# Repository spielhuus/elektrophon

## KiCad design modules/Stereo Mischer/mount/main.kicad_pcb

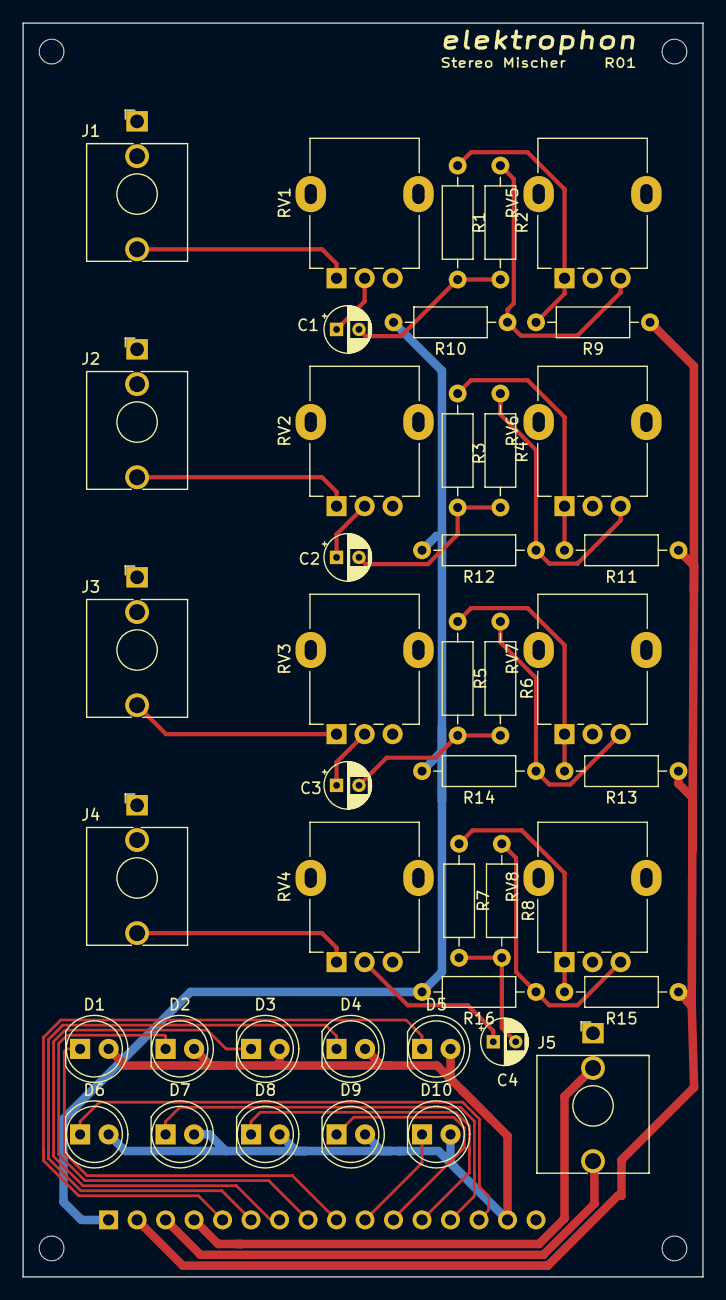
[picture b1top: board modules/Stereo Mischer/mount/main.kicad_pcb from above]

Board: 2 copper layers, 60.6 x 111.8 mm, 44 parts (1 on the bottom side), 36 nets.

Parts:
C1, C2, C3, C4: 4u7; CP_Radial_D4.0mm_P2.00mm
D1, D2, D3, D4, D5, D6, D7, D8, D9, D10: LED; LED_D5.0mm
J1: #1; Jack_3.5mm_WQP-PJ398SM_Vertical
J2: #2; Jack_3.5mm_WQP-PJ398SM_Vertical
J3: #3; Jack_3.5mm_WQP-PJ398SM_Vertical
J4: #4; Jack_3.5mm_WQP-PJ398SM_Vertical
J5: STEREO_OUT; Jack_3.5mm_WQP-PJ301BM_Vertical
J6: Conn_01x16_Male; PinHeader_1x16_P2.54mm_Vertical
R1, R2, R3, R4, R5, R6, R7, R8, R9, R10, R11, R12, R13, R14, R15, R16: 10k; R_Axial_DIN0207_L6.3mm_D2.5mm_P10.16mm_Horizontal
RV1, RV2, RV3, RV4: 10k; Potentiometer_Alpha_RD901F-40-00D_Single_Vertical
RV5, RV6, RV7, RV8: 25k; Potentiometer_Alpha_RD901F-40-00D_Single_Vertical

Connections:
+15V: D1.2, D2.2, D3.2, D4.2, D5.2, D6.2, D7.2, D8.2, D9.2, D10.2, J6.15
/LED_L_1: D6.1, J6.14
/LED_L_2: D7.1, J6.13
/LED_L_3: D8.1, J6.12
/LED_L_4: D9.1, J6.11
/LED_L_5: D10.1, J6.10
/LED_R_1: D1.1, J6.9
/LED_R_2: D2.1, J6.8
/LED_R_3: D3.1, J6.7
/LED_R_4: D4.1, J6.6
/LED_R_5: D5.1, J6.5
/LEFT: J6.2, R9.1, R11.1, R13.1, R15.1
/RIGHT: J6.1, R10.2, R12.2, R14.2, R16.2
/STEREO_L: J5.R, J6.4
/STEREO_R: J5.T, J6.3
GND: J1.S, J2.S, J3.S, J4.S, J5.S, J6.16, RV1.3, RV2.3, RV3.3, RV4.3, RV5.2, RV6.2, RV7.2, RV8.2
unnamed: C1.1, RV1.2
unnamed: C1.2, R1.2, R2.2
unnamed: C2.1, RV2.2
unnamed: C2.2, R3.2, R4.2
unnamed: C3.1, RV3.2
unnamed: C3.2, R5.2, R6.2
unnamed: C4.1, RV4.2
unnamed: C4.2, R7.2, R8.2
unnamed: J1.T, RV1.1
unnamed: J2.T, RV2.1
unnamed: J3.T, RV3.1
unnamed: J4.T, RV4.1
unnamed: R1.1, R9.2, RV5.1
unnamed: R2.1, R10.1, RV5.3
unnamed: R3.1, R11.2, RV6.1
unnamed: R4.1, R12.1, RV6.3
unnamed: R5.1, R13.2, RV7.1
unnamed: R6.1, R14.1, RV7.3
unnamed: R7.1, R15.2, RV8.1
unnamed: R8.1, R16.1, RV8.3

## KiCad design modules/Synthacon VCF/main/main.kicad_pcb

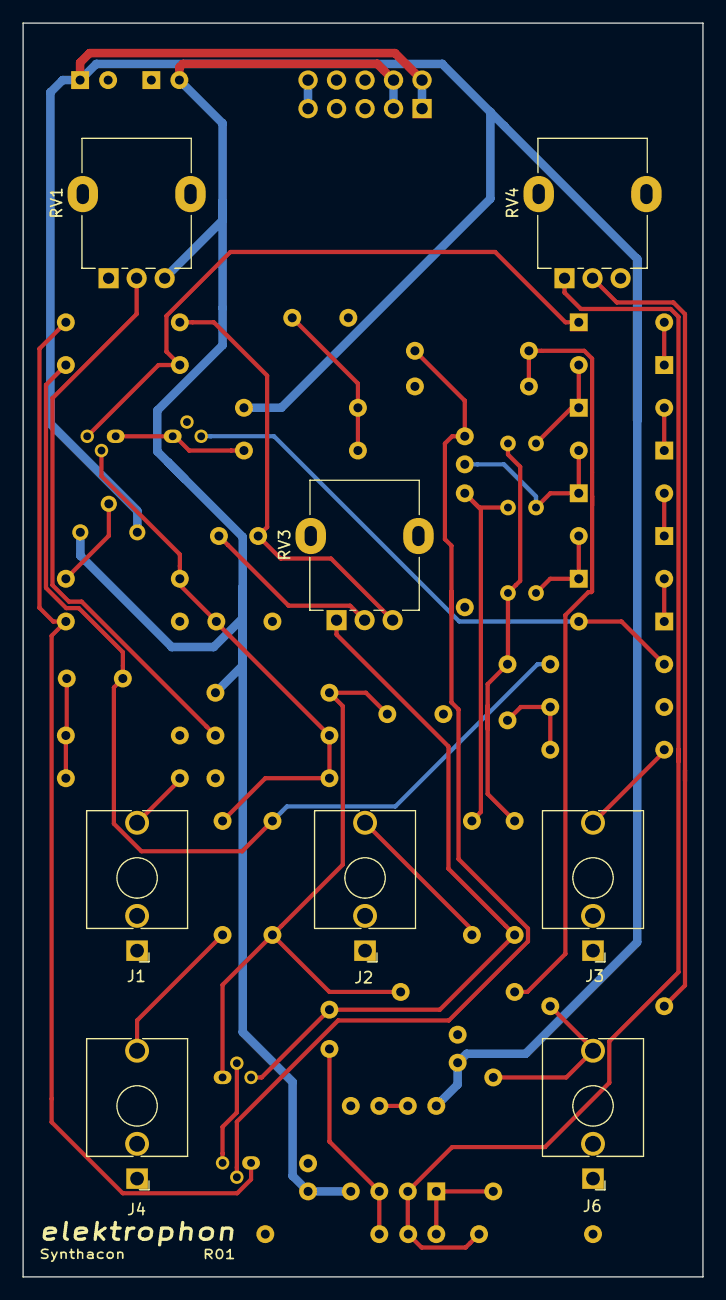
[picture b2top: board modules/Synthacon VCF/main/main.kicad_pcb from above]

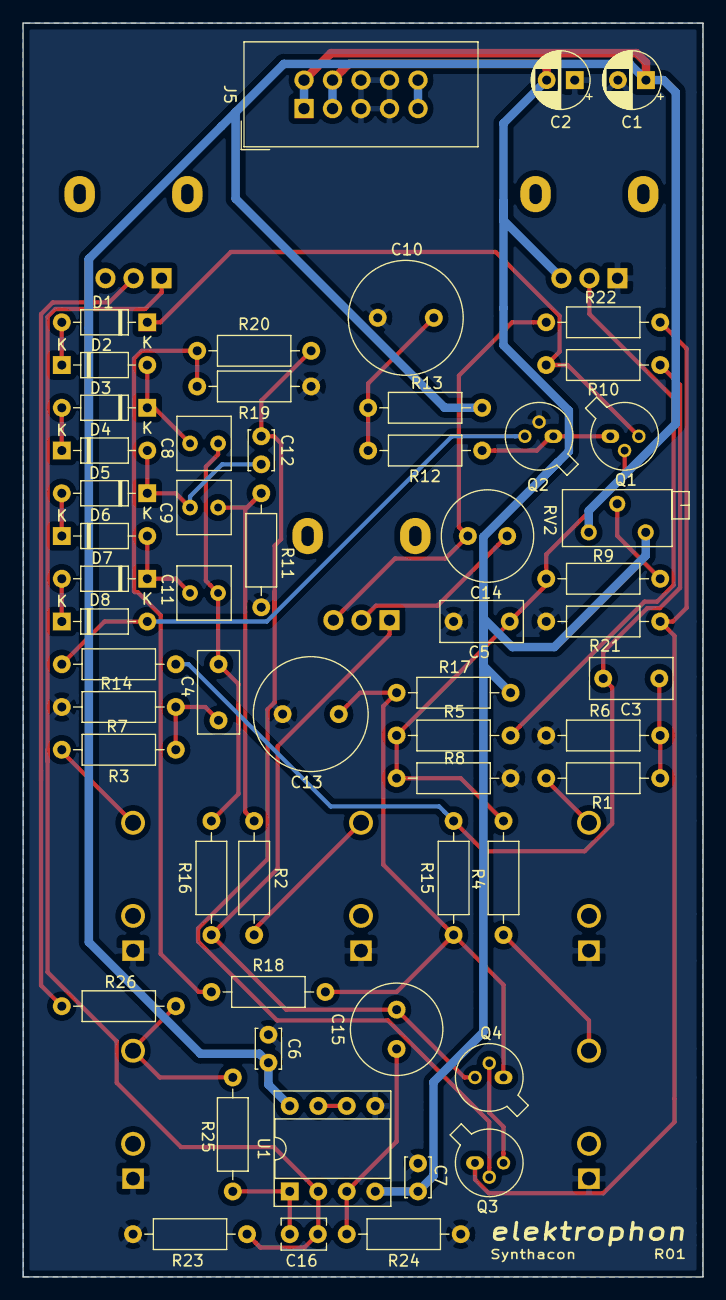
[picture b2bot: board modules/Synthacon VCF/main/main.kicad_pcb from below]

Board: 2 copper layers, 60.6 x 111.8 mm, 65 parts (57 on the bottom side), 41 nets.

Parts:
C1, C2: 10u; CP_Radial_D5.0mm_P2.50mm
C3, C4, C5: 1u; C_Rect_L7.2mm_W3.5mm_P5.00mm_FKS2_FKP2_MKS2_MKP2
C6, C7: 0.1u; C_Disc_D3.4mm_W2.1mm_P2.50mm
C8, C9, C11: 2n2; C_Rect_L4.6mm_W4.6mm_P2.50mm_MKS02_FKP02
C10, C13: 47u; C_Radial_D10.0mm_H20.0mm_P5.00mm
C12: 100n; C_Disc_D3.4mm_W2.1mm_P2.50mm
C14, C15: 10u; C_Radial_D8.0mm_H7.0mm_P3.50mm
C16: 47p; C_Disc_D3.8mm_W2.6mm_P2.50mm
D1, D2, D3, D4, D5, D6, D7, D8: 1N4148; D_DO-35_SOD27_P7.62mm_Horizontal
J1: LP; Jack_3.5mm_QingPu_WQP-PJ398SM_Vertical_CircularHoles
J2: HP; Jack_3.5mm_QingPu_WQP-PJ398SM_Vertical_CircularHoles
J3: BP; Jack_3.5mm_QingPu_WQP-PJ398SM_Vertical_CircularHoles
J4: CV; Jack_3.5mm_QingPu_WQP-PJ398SM_Vertical_CircularHoles
J5: IDC Header; IDC-Header_2x05_P2.54mm_Vertical
J6: out; Jack_3.5mm_QingPu_WQP-PJ398SM_Vertical_CircularHoles
Q1, Q2, Q3: 2n2222; TO-18-3
Q4: 2N2907; TO-18-3
R1, R2, R3, R26: 47k; R_Axial_DIN0207_L6.3mm_D2.5mm_P10.16mm_Horizontal
R4, R5, R9: 220k; R_Axial_DIN0207_L6.3mm_D2.5mm_P10.16mm_Horizontal
R6: 390k; R_Axial_DIN0207_L6.3mm_D2.5mm_P10.16mm_Horizontal
R7: 180k; R_Axial_DIN0207_L6.3mm_D2.5mm_P10.16mm_Horizontal
R8, R11, R15, R16, R22: 1k; R_Axial_DIN0207_L6.3mm_D2.5mm_P10.16mm_Horizontal
R10, R14, R19, R21: 2k2; R_Axial_DIN0207_L6.3mm_D2.5mm_P10.16mm_Horizontal
R12: 3k9; R_Axial_DIN0207_L6.3mm_D2.5mm_P10.16mm_Horizontal
R13: 82; R_Axial_DIN0207_L6.3mm_D2.5mm_P10.16mm_Horizontal
R17: 390; R_Axial_DIN0207_L6.3mm_D2.5mm_P10.16mm_Horizontal
R18: 8k2; R_Axial_DIN0207_L6.3mm_D2.5mm_P10.16mm_Horizontal
R20: 2m2; R_Axial_DIN0207_L6.3mm_D2.5mm_P10.16mm_Horizontal
R23: 10k; R_Axial_DIN0207_L6.3mm_D2.5mm_P10.16mm_Horizontal
R24: 100k; R_Axial_DIN0207_L6.3mm_D2.5mm_P10.16mm_Horizontal
R25: 330; R_Axial_DIN0207_L6.3mm_D2.5mm_P10.16mm_Horizontal
RV1, RV4: 100k; Potentiometer_Alpha_RD901F-40-00D_Single_Vertical
RV2: 100k; Potentiometer_Bourns_3296Z_Horizontal
RV3: 1k; Potentiometer_Alpha_RD901F-40-00D_Single_Vertical
U1: TL072; DIP-8_W7.62mm_Socket

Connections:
+5V: J5.9, J5.10
+15V: C2.2, C7.1, J5.3, J5.4, R17.2, RV1.3, RV2.3, U1.4
-15V: C1.1, C6.2, J5.1, J5.2, R13.1, RV2.1, U1.8
GND: C1.2, C2.1, C5.1, C6.1, C7.2, C10.2, C13.1, J1.S, J2.S, J3.S, J4.S, J5.5, J5.6, J5.7, J5.8, J6.S, Q2.2, R6.1, R7.1, R8.1, R11.1, R19.1, R21.1, R23.1, R24.1, RV1.1, U1.5
unnamed: C3.1, R10.2, R14.2, R15.2
unnamed: C3.2, R1.1, R6.2
unnamed: C4.2, R3.1, R7.2
unnamed: C5.2, Q1.2, R4.1, R5.1, R8.2, R9.2
unnamed: C8.1, D2.2, D3.1
unnamed: C9.2, R2.1, R11.2
unnamed: C10.1, R12.1, R13.2
unnamed: C11.1, D6.2, D7.1
unnamed: C4.1, C8.2, C11.2, R16.2
unnamed: C12.1, Q3.2, R20.2
unnamed: C9.1, C12.2, D4.2, D5.1
unnamed: C13.2, Q4.1, R15.1, R17.1, R18.2
unnamed: C14.1, R22.1, RV3.3
unnamed: C14.2, RV3.2
unnamed: C15.1, R24.2, U1.3
unnamed: C15.2, Q4.3, R16.1, RV3.1
unnamed: C16.1, R25.2, U1.1
unnamed: C16.2, R23.2, RV4.1, U1.2
unnamed: D1.1, Q1.3, R10.1
unnamed: D1.2, D2.1
unnamed: D3.2, D4.1
unnamed: D5.2, D6.1
unnamed: D7.2, D8.1
unnamed: D8.2, Q2.3, R14.1
unnamed: J1.T, R1.2
unnamed: J2.T, R2.2
unnamed: J3.T, R3.2
unnamed: J4.T, R4.2
unnamed: J6.T, R25.1, R26.1
unnamed: Q1.1, Q2.1, R12.2
unnamed: Q3.1, R21.2, R22.2
unnamed: Q3.3, Q4.2
unnamed: R5.2, RV1.2
unnamed: R9.1, RV2.2
unnamed: R18.1, R19.2, R20.1
unnamed: R26.2, RV4.2
unnamed: U1.6, U1.7

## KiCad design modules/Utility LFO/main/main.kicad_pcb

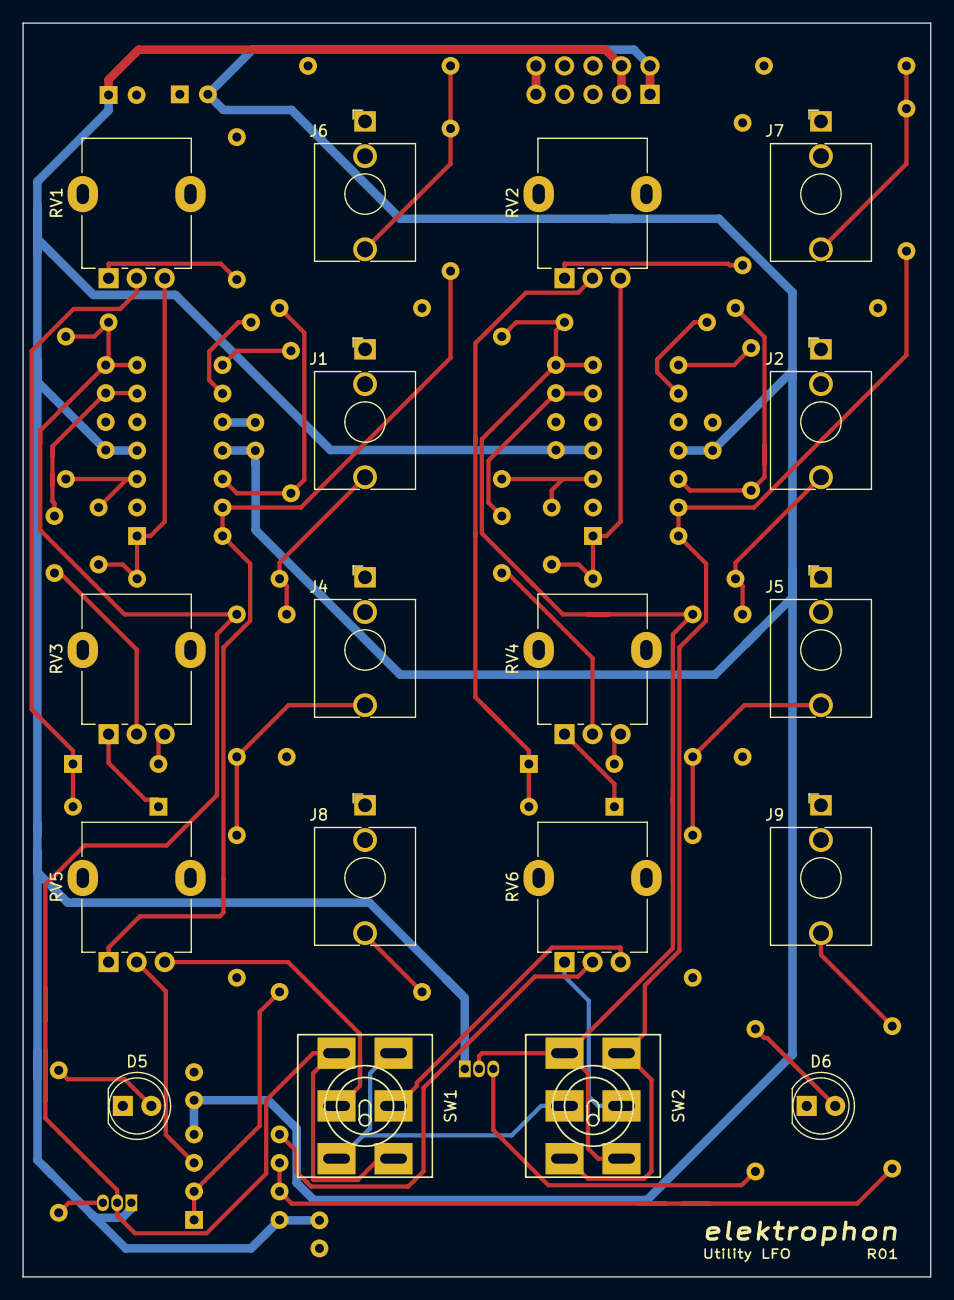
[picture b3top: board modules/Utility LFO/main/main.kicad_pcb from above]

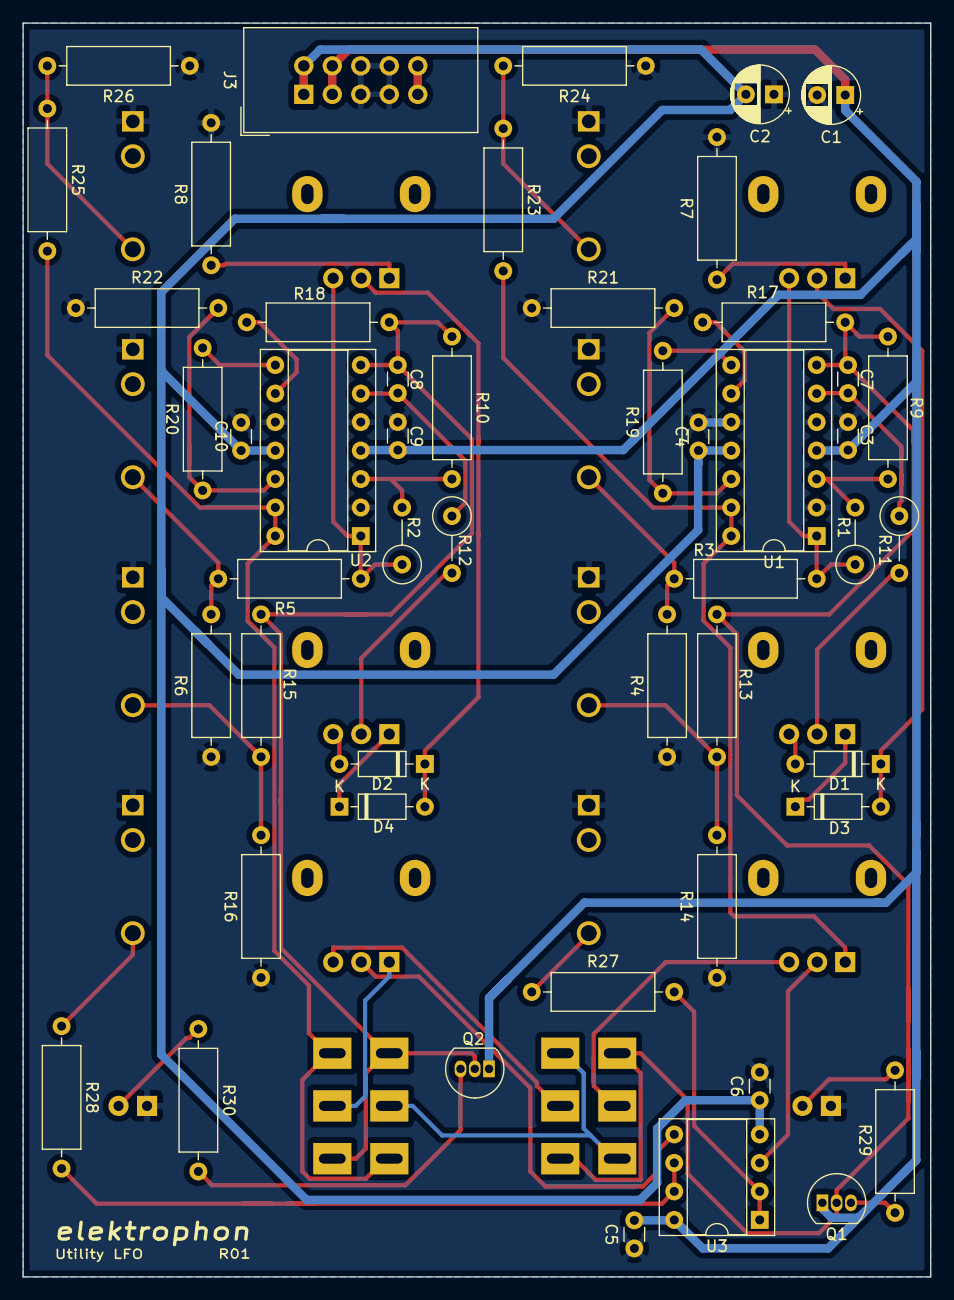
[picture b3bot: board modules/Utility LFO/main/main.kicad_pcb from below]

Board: 2 copper layers, 80.9 x 111.8 mm, 68 parts (50 on the bottom side), 50 nets.

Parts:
C1, C2: 10u; CP_Radial_D5.0mm_P2.50mm
C3, C4, C5, C6, C9, C10: 100n; C_Disc_D3.0mm_W1.6mm_P2.50mm
C7, C8: 47n; C_Disc_D3.0mm_W1.6mm_P2.50mm
D1, D2, D3, D4: D; D_DO-35_SOD27_P7.62mm_Horizontal
D5, D6: LED; LED_D5.0mm
J1, J2: PULSE; Jack_3.5mm_QingPu_WQP-PJ398SM_Vertical_CircularHoles
J3: IDC Header; IDC-Header_2x05_P2.54mm_Vertical
J4, J5: TRI/SAW; Jack_3.5mm_QingPu_WQP-PJ398SM_Vertical_CircularHoles
J6, J7: square; Jack_3.5mm_QingPu_WQP-PJ398SM_Vertical_CircularHoles
J8, J9: vari; Jack_3.5mm_QingPu_WQP-PJ398SM_Vertical_CircularHoles
Q1, Q2: BC547; TO-92_Inline
R1, R2: 150k; R_Axial_DIN0309_L9.0mm_D3.2mm_P5.08mm_Vertical
R3, R5: 2k2; R_Axial_DIN0309_L9.0mm_D3.2mm_P12.70mm_Horizontal
R4, R6, R13, R14, R15, R16, R23, R24, R25, R26, R27, R28, R29, R30: 1k; R_Axial_DIN0309_L9.0mm_D3.2mm_P12.70mm_Horizontal
R7, R8: 4k7; R_Axial_DIN0309_L9.0mm_D3.2mm_P12.70mm_Horizontal
R9, R10, R17, R18, R21, R22: 100k; R_Axial_DIN0309_L9.0mm_D3.2mm_P12.70mm_Horizontal
R11, R12: 10k; R_Axial_DIN0309_L9.0mm_D3.2mm_P5.08mm_Vertical
R19, R20: 47k; R_Axial_DIN0309_L9.0mm_D3.2mm_P12.70mm_Horizontal
RV1, RV2, RV5, RV6: 100k; Potentiometer_Alpha_RD901F-40-00D_Single_Vertical
RV3, RV4: 500k; Potentiometer_Alpha_RD901F-40-00D_Single_Vertical
SW1, SW2: SW_DPDT_x2; Tumbler_SW_x2
U1, U2: TL074; DIP-14_W7.62mm_Socket
U3: TL072; DIP-8_W7.62mm_Socket

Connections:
+5V: J3.9, J3.10
+15V: C1.1, C3.2, C5.2, C9.2, J3.3, J3.4, Q1.1, Q2.1, U1.4, U2.4, U3.8
-15V: C2.2, C4.1, C6.1, C10.1, J3.1, J3.2, U1.11, U2.11, U3.4
/VARI1_a: RV5.3, SW1.5
/VARI1_b: C7.1, Q1.2, R9.1, R13.2, R17.2, SW1.1, SW1.6, U1.7
/VARI2_a: RV6.3, SW1.2
/VARI2_b: C8.1, Q2.2, R10.1, R15.2, R18.2, SW2.1, SW2.6, U2.7
/VARI2_c: R25.2, SW2.3, SW2.4, U2.13, U2.14
/VARI2_d: RV6.1, SW2.2
GND: C1.2, C2.1, C3.1, C4.2, C5.1, C6.2, C9.1, C10.2, D5.1, D6.1, J1.S, J2.S, J3.5, J3.6, J3.7, J3.8, J4.S, J5.S, J6.S, J7.S, J8.S, J9.S, R4.1, R6.1, R7.2, R8.2, R14.1, R16.1, R21.1, R22.1, R24.1, R26.1, U1.2, U1.5, U1.10, U2.2, U2.5, U2.10
unnamed: C7.2, R11.1, U1.6
unnamed: C8.2, R12.1, U2.6
unnamed: D1.1, D3.2, RV1.2
unnamed: D1.2, RV3.3
unnamed: D2.1, D4.2, RV2.2
unnamed: D2.2, RV4.3
unnamed: D3.1, RV3.1
unnamed: D4.1, RV4.1
unnamed: D5.2, R29.1
unnamed: D6.2, R30.1
unnamed: J1.T, R3.1, R4.2
unnamed: J2.T, R5.1, R6.2
unnamed: J4.T, R13.1, R14.2
unnamed: J5.T, R15.1, R16.2
unnamed: J6.T, R23.1, R24.2
unnamed: J7.T, R25.1, R26.2
unnamed: J8.T, R27.1
unnamed: J9.T, R28.1
unnamed: Q1.3, R29.2
unnamed: Q2.3, R30.2
unnamed: R1.1, R3.2, RV1.3, U1.1
unnamed: R1.2, R9.2, U1.3
unnamed: R2.1, R5.2, RV2.3, U2.1
unnamed: R7.1, RV1.1
unnamed: R8.1, RV2.1
unnamed: R2.2, R10.2, U2.3
unnamed: R11.2, RV3.2
unnamed: R12.2, RV4.2
unnamed: R17.1, U1.9
unnamed: R18.1, U2.9
unnamed: R19.1, R21.2, U1.12
unnamed: R19.2, U1.8
unnamed: R20.1, R22.2, U2.12
unnamed: R20.2, U2.8
unnamed: R23.2, RV5.1, U1.13, U1.14
unnamed: R27.2, U3.1, U3.2
unnamed: R28.2, U3.6, U3.7
unnamed: RV5.2, U3.3
unnamed: RV6.2, U3.5
unnamed: SW1.3, SW1.4, SW2.5

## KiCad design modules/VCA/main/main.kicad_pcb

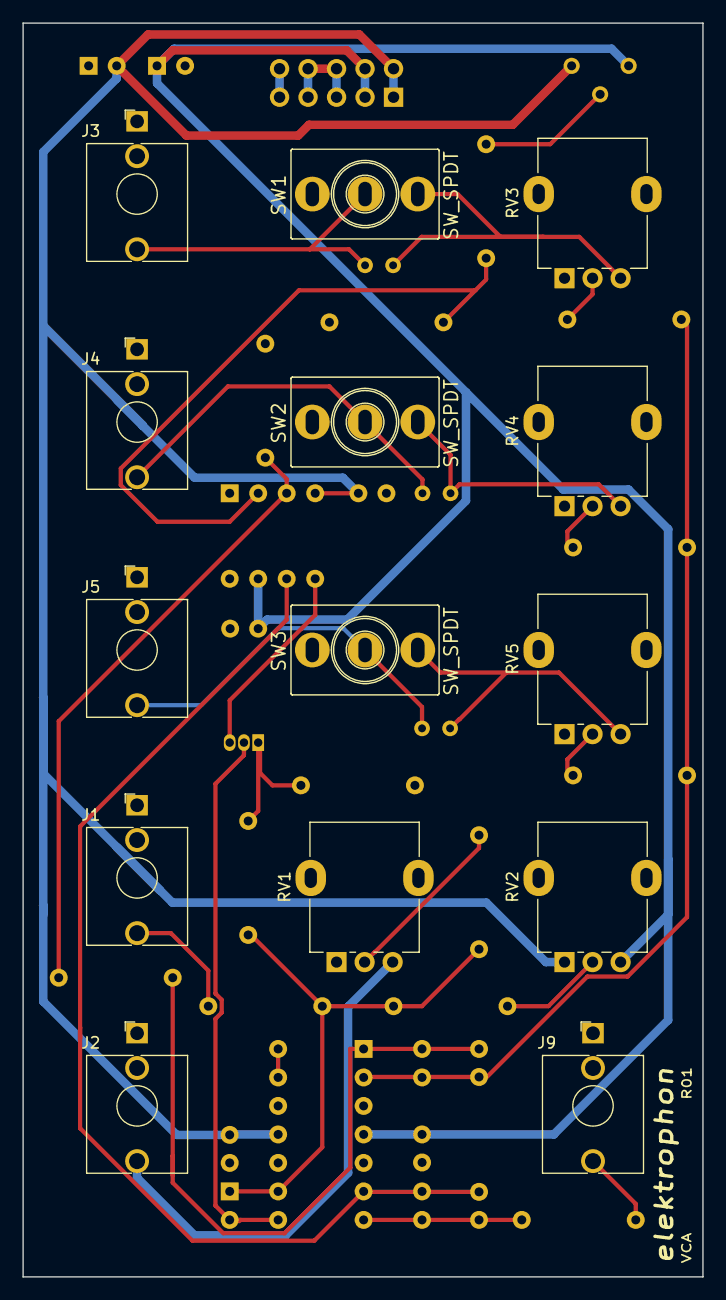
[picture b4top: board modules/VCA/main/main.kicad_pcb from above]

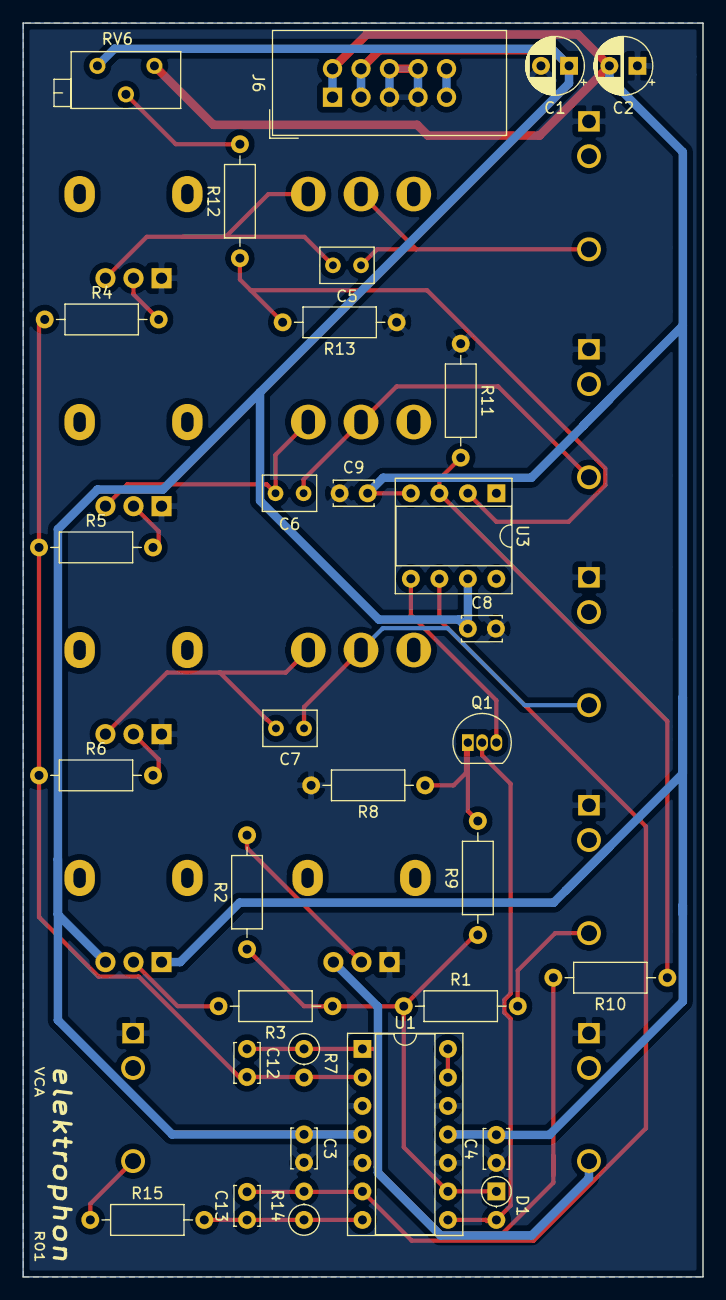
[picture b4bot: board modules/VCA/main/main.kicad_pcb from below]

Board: 2 copper layers, 60.6 x 111.8 mm, 46 parts (32 on the bottom side), 30 nets.

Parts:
C1, C2: 10u; CP_Radial_D5.0mm_P2.50mm
C3, C4, C8, C9: 0.1u; C_Disc_D3.4mm_W2.1mm_P2.50mm
C5, C6, C7: 0.22u; C_Rect_L4.6mm_W3.0mm_P2.50mm_MKS02_FKP02
C12: 10p; C_Disc_D3.4mm_W2.1mm_P2.50mm
C13: 22p; C_Disc_D3.4mm_W2.1mm_P2.50mm
D1: 1N4148; D_DO-35_SOD27_P2.54mm_Vertical_AnodeUp
J1: Envelope; Jack_3.5mm_QingPu_WQP-PJ398SM_Vertical_CircularHoles
J2: CV; Jack_3.5mm_QingPu_WQP-PJ398SM_Vertical_CircularHoles
J3: #1; Jack_3.5mm_QingPu_WQP-PJ398SM_Vertical_CircularHoles
J4: #2; Jack_3.5mm_QingPu_WQP-PJ398SM_Vertical_CircularHoles
J5: #3; Jack_3.5mm_QingPu_WQP-PJ398SM_Vertical_CircularHoles
J6: POWER; IDC-Header_2x05_P2.54mm_Vertical
J9: OUT; Jack_3.5mm_QingPu_WQP-PJ398SM_Vertical_CircularHoles
Q1: 2N3906; TO-92_Inline
R1, R2, R4, R5, R6, R9, R12: 100k; R_Axial_DIN0207_L6.3mm_D2.5mm_P10.16mm_Horizontal
R3: 330k; R_Axial_DIN0207_L6.3mm_D2.5mm_P10.16mm_Horizontal
R7: 100k; R_Axial_DIN0207_L6.3mm_D2.5mm_P2.54mm_Vertical
R8, R10: 11k; R_Axial_DIN0207_L6.3mm_D2.5mm_P10.16mm_Horizontal
R11, R13: 22; R_Axial_DIN0207_L6.3mm_D2.5mm_P10.16mm_Horizontal
R14: 51k; R_Axial_DIN0207_L6.3mm_D2.5mm_P2.54mm_Vertical
R15: 1k; R_Axial_DIN0207_L6.3mm_D2.5mm_P10.16mm_Horizontal
RV1, RV2, RV3, RV4, RV5: 100k; Potentiometer_Alpha_RD901F-40-00D_Single_Vertical
RV6: 100k; Potentiometer_Bourns_3296Z_Horizontal
SW1, SW2, SW3: SW_SPDT; SPDT_KIT
U1: TL074; DIP-14_W7.62mm_Socket
U3: CA3080; DIP-8_W7.62mm_Socket

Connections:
+5V: J6.9, J6.10
+15V: C1.1, C3.1, C8.1, J6.3, J6.4, RV2.3, RV6.3, U1.4, U3.7
-15V: C2.2, C4.2, C9.2, J6.1, J6.2, RV2.1, RV6.1, U1.11, U3.4
GND: C1.2, C2.1, C3.2, C4.1, C8.2, C9.1, J1.S, J2.S, J3.S, J4.S, J5.S, J6.5, J6.6, J6.7, J6.8, J9.S, R8.2, R11.1, R13.1, RV1.1, RV3.1, RV4.1, RV5.1, U1.3, U1.5, U1.10, U1.12
unnamed: C5.1, J3.T, SW1.2
unnamed: C5.2, RV3.3, SW1.3
unnamed: C6.1, J4.T, SW2.2
unnamed: C6.2, RV4.3, SW2.3
unnamed: C7.1, J5.T, SW3.2
unnamed: C7.2, RV5.3, SW3.3
unnamed: C12.1, R7.1, R10.2, U1.1
unnamed: C12.2, R4.1, R5.1, R6.1, R7.2, U1.2
unnamed: C13.1, R14.1, R15.2, U1.7
unnamed: C13.2, R14.2, U1.6, U3.6
unnamed: D1.1, R1.1, R2.1, R3.1, R9.1, U1.9
unnamed: D1.2, Q1.2, U1.8
unnamed: J1.T, R1.2
unnamed: J2.T, RV1.3
unnamed: J9.T, R15.1
unnamed: Q1.1, R8.1, R9.2
unnamed: Q1.3, U3.5
unnamed: R2.2, RV1.2
unnamed: R3.2, RV2.2
unnamed: R4.2, RV3.2
unnamed: R5.2, RV4.2
unnamed: R6.2, RV5.2
unnamed: R10.1, R11.2, U3.3
unnamed: R12.1, R13.2, U3.2
unnamed: R12.2, RV6.2
unnamed: U1.13, U1.14

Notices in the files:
modules/Stereo Mischer/mount/main.kicad_pcb:
License CC BY 4.0 - Attribution 4.0 International
